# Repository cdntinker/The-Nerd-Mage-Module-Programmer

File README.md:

# This is __The Nerd Mage Module Programmer__  Project

The original intent of this project was to simplify pre-programming ESP modules.

I started out doing up a design to help a friend program ESP-M3 modules with OTA capable firmware that he could then solder into projects to be scattered around And never directly connected again.

And, of course, The rabbits showed up & started digging holes in my desktop...  As usual...

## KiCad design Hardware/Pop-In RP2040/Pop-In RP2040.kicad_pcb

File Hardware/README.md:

# This is __The Nerd Mage Module Programmer__  Project

Each of the subfolders here is basically a KiCAD project.  Yes, I know there's a lot of duplication here.  One of these days, I'll figure out how to make KiCAD re-use existing schematics & board files as "libraries".

- (KiCAD Customs)
  - Custom symbols, footprints, 3D models needed for this project
    - (Just the 3D models so far...)

## The various "editions"...

- (blank)
  - The base design with no module set up
- (standalone)
  - A version with a pin header instead of a module
- ESP-01F
  - Footprint added for an ESP-01F
- ESP-01S
  - Footprint added for an ESP-01S
- ESP-M3
  - Footprint added for an ESP-M3
- ESP-12
  - Footprint added for an ESP-12 (or ESP-07)
- ESP-Wroom-32
  - Footprint added for an ESP-Wroom-32
- Seeed Wio-RP2040
  - This one is VERY MUCH a WIP
  - Building & adding a footprint for the Seeed Studios Wio-RP2040 module
- BOM.ods
  - Sort of a manually created Bill of Materials

  ## To be done

  Need to work out how to add my custom symbols, footprints & 3D models in here...

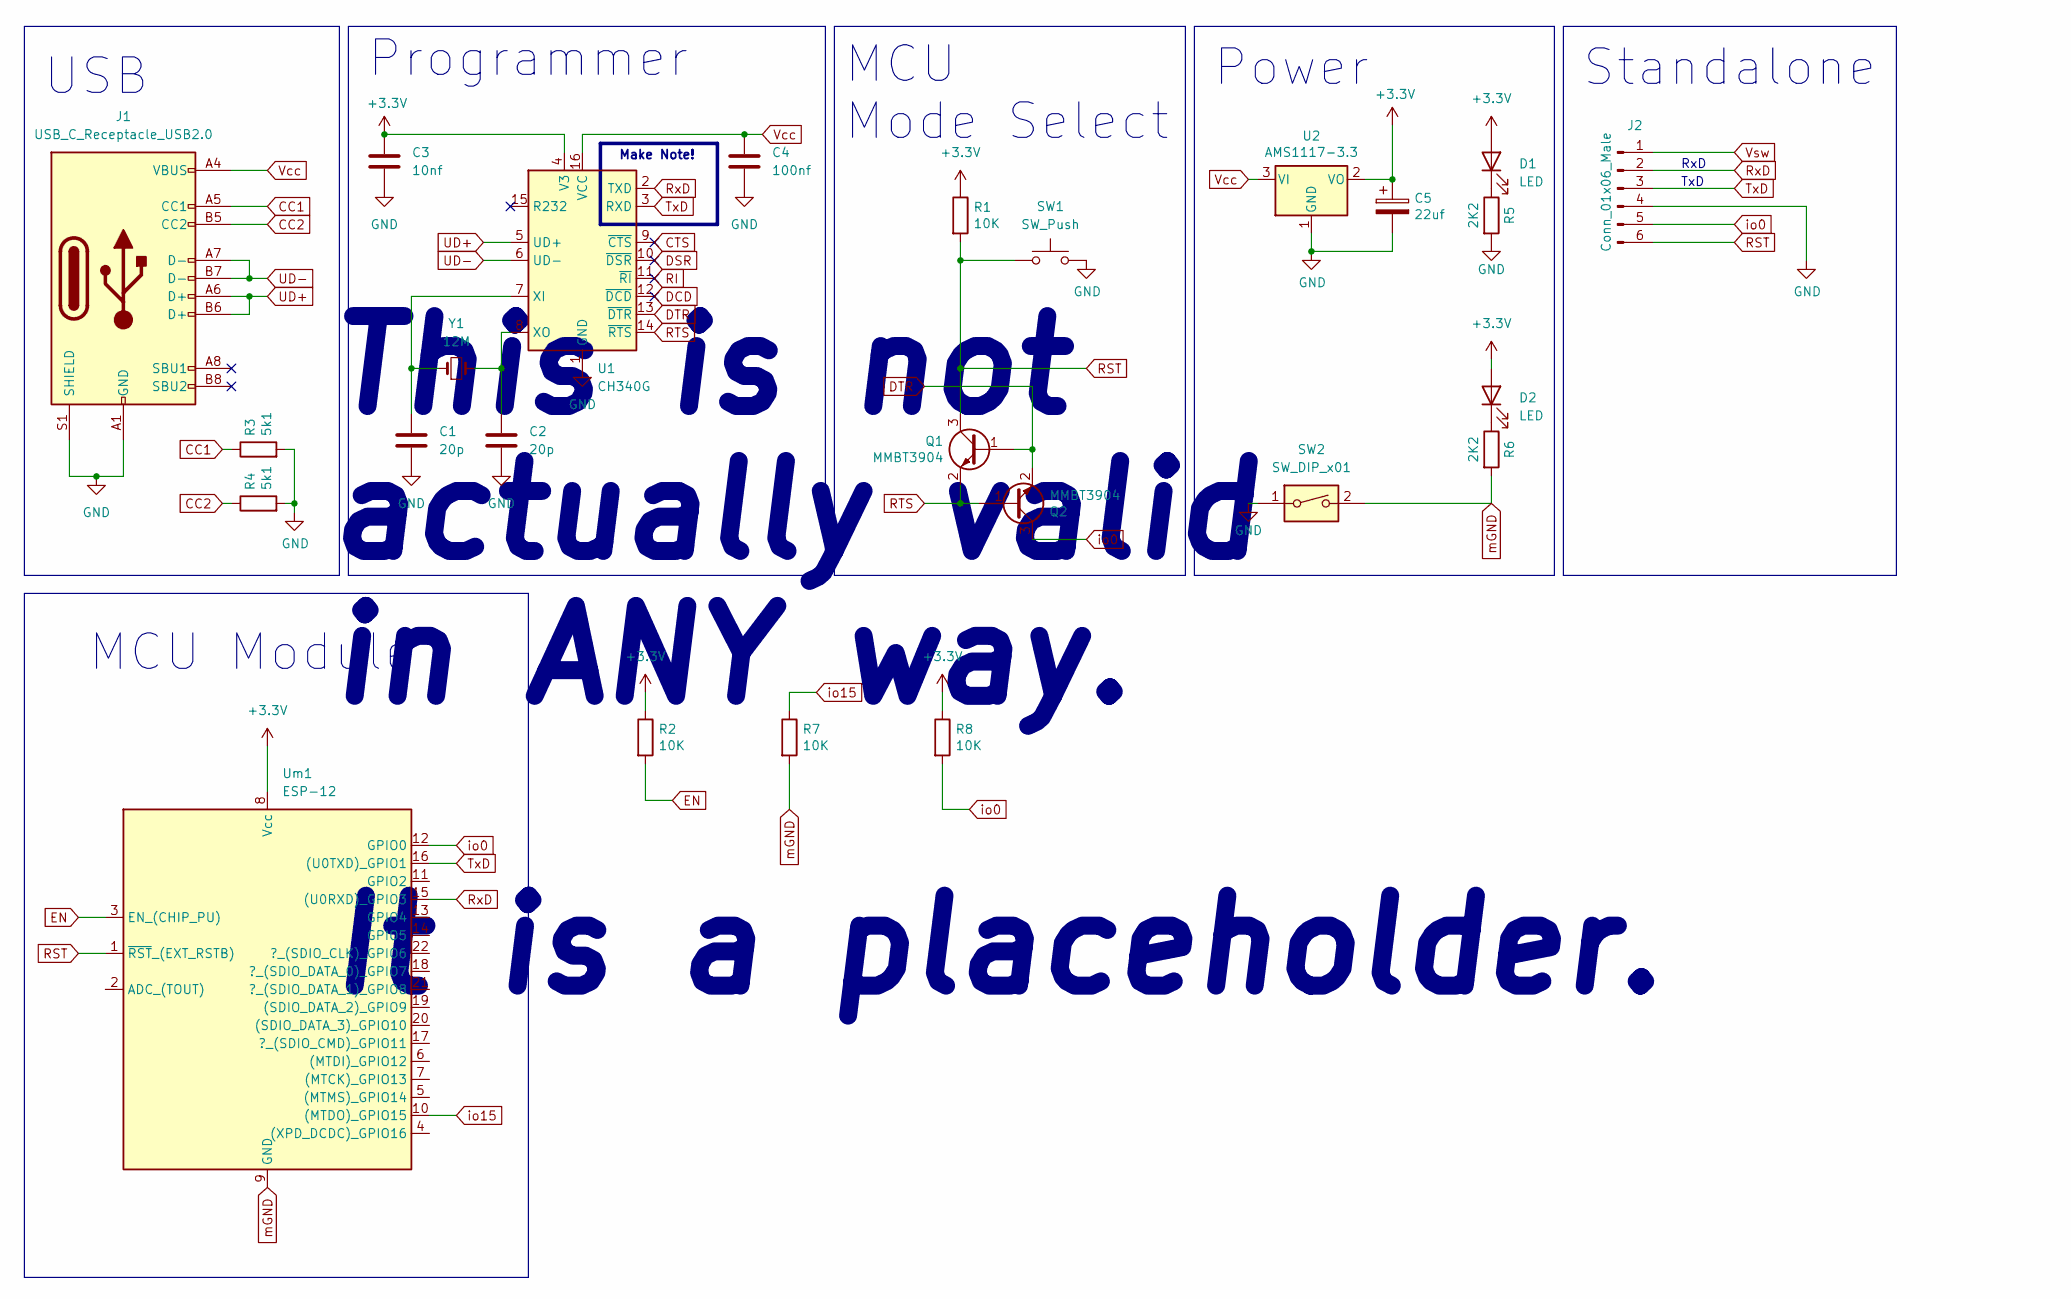
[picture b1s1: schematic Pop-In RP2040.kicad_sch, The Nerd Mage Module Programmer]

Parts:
C1, C2: 20p; C_0603_1608Metric_Pad1.08x0.95mm_HandSolder; LCSC C408549 (20pf C325469)
C3: 10nf; C_0603_1608Metric_Pad1.08x0.95mm_HandSolder; LCSC C161232
C4: 100nf; C_0603_1608Metric_Pad1.08x0.95mm_HandSolder; LCSC C235731
C5: 22uf; CP_EIA-6032-28_Kemet-C_Pad2.25x2.35mm_HandSolder
D1, D2: LED; LED_0805_2012Metric_Pad1.15x1.40mm_HandSolder
J1: USB_C_Receptacle_USB2.0; USB_C_Receptacle_HRO_TYPE-C-31-M-12
J2: Conn_01x06_Male; PinHeader_1x06_P2.54mm_Vertical
Q1, Q2: MMBT3904; SOT-23_Handsoldering
R1, R2, R7, R8: 10K; R_0603_1608Metric_Pad0.98x0.95mm_HandSolder
R3, R4: 5k1; R_0603_1608Metric_Pad0.98x0.95mm_HandSolder
R5, R6: 2K2; R_0603_1608Metric_Pad0.98x0.95mm_HandSolder
SW1: SW_Push; SW_Push_TS273014TP; LCSC C2858276
SW2: SW_DIP_x01; SW_DIP_SPSTx01_Slide_6.7x4.1mm_W7.62mm_P2.54mm_LowProfile
U1: CH340G; SOIC-16_3.9x9.9mm_P1.27mm; LCSC C14267
U2: AMS1117-3.3; SOT-223-3_TabPin2
Um1: ESP-12; ESP-12 (FlexyPin)
Y1: 12M; Crystal_SMD_5032-2Pin_5.0x3.2mm; LCSC C2842275

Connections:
+3.3V: C3.1, C5.1, D1.2 (A), D2.2 (A), R1.1, R2.1, R8.1, U1.4 (V3), U2.2 (VO), Um1.8 (Vcc)
CC1: J1.A5 (CC1), R3.1
CC2: J1.B5 (CC2), R4.1
CTS: U1.9 (~CTS)
DCD: U1.12 (~DCD)
DSR: U1.10 (~DSR)
DTR: Q1.1 (B), Q2.2 (E), U1.13 (~DTR)
EN: R2.2, Um1.3 (EN_(CHIP_PU))
GND: C1.2, C2.2, C3.2, C4.2, C5.2, J1.A1 (GND), J1.A12 (GND), J1.B1 (GND), J1.B12 (GND), J1.S1 (SHIELD), J2.4, R3.2, R4.2, R5.2, SW1.2, SW2.1, U1.1 (GND), U2.1 (GND)
unnamed: C1.1, U1.7 (XI), Y1.1
unnamed: C2.1, U1.8 (XO), Y1.2
unnamed: D1.1 (K), R5.1
unnamed: D2.1 (K), R6.1
RI: U1.11 (~RI)
RST: J2.6, Q1.3 (C), R1.2, SW1.1, Um1.1 (~RST_(EXT_RSTB))
RTS: Q1.2 (E), Q2.1 (B), U1.14 (~RTS)
RxD: J2.2, U1.2 (TXD), Um1.15 ((U0RXD)_GPIO3)
TxD: J2.3, U1.3 (RXD), Um1.16 ((U0TXD)_GPIO1)
UD+: J1.A6 (D+), J1.B6 (D+), U1.5 (UD+)
UD-: J1.A7 (D-), J1.B7 (D-), U1.6 (UD-)
Vcc: C4.1, J1.A4 (VBUS), J1.A9 (VBUS), J1.B4 (VBUS), J1.B9 (VBUS), U1.16 (VCC), U2.3 (VI)
io0: J2.5, Q2.3 (C), R8.2, Um1.12 (GPIO0)
io15: R7.1, Um1.10 ((MTDO)_GPIO15)
mGND: R6.2, R7.2, SW2.2, Um1.9 (GND)

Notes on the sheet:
Make Note!
Power
USB
MCU Mode Select
TxD
Standalone
This is not actually valid in ANY way. It is a placeholder.
RxD
MCU Module
Programmer

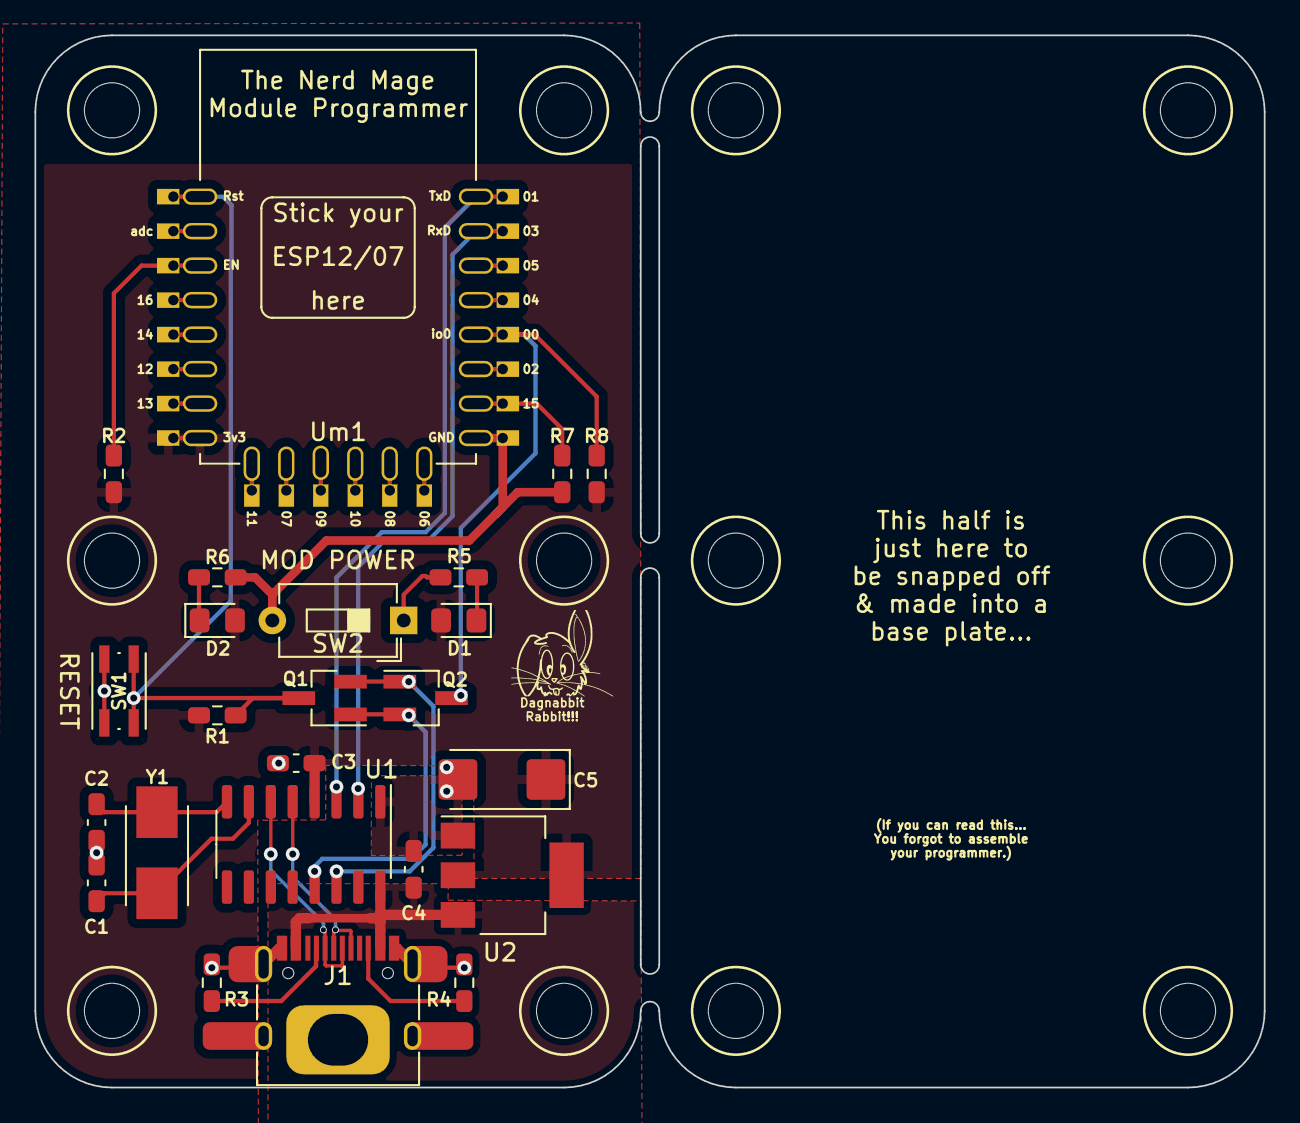
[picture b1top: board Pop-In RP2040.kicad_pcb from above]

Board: 2 copper layers, 71.3 x 61.0 mm, 24 parts (0 on the bottom side), 20 nets.

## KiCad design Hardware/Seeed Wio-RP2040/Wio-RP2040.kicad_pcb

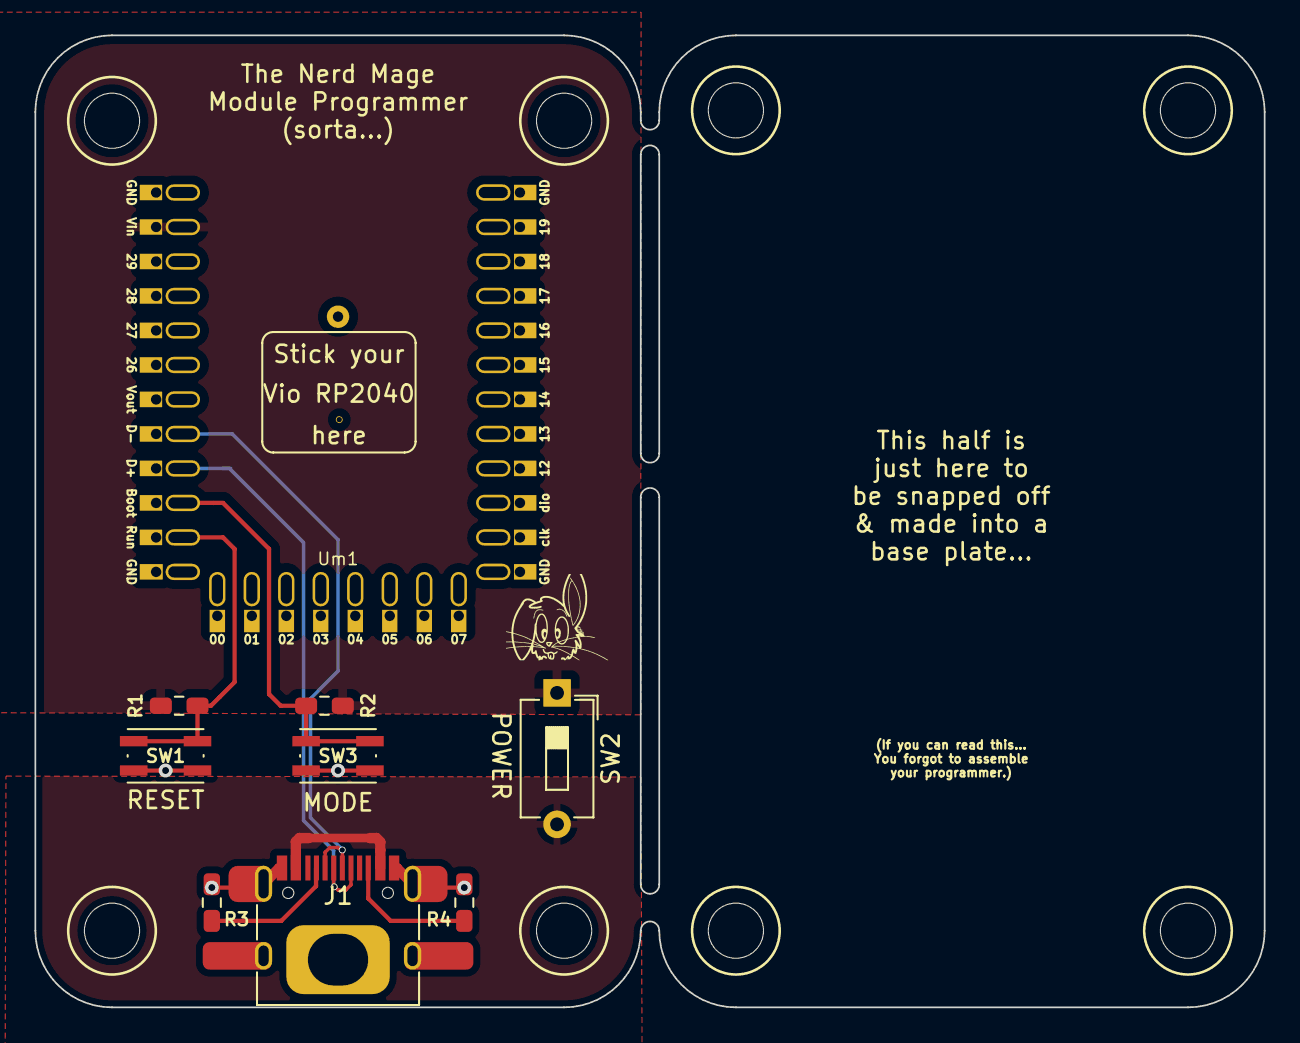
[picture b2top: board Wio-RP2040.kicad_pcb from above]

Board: 2 copper layers, 71.3 x 56.4 mm, 9 parts (0 on the bottom side), 9 nets.

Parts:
J1: USB_C_Receptacle_USB2.0; USB_C_Receptacle_HRO_TYPE-C-31-M-12
R1, R2: 10K; R_0603_1608Metric_Pad0.98x0.95mm_HandSolder
R3, R4: 5k1; R_0603_1608Metric_Pad0.98x0.95mm_HandSolder
SW1, SW3: SW_Push; SW_Push_TS273014TP
SW2: SW_DIP_x01; SW_DIP_SPSTx01_Slide_6.7x4.1mm_W7.62mm_P2.54mm_LowProfile
Um1: Wio-RP2040; Wio_RP2040 (FlexyPin)

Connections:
CC1: J1.A5 (CC1), R3.1
CC2: J1.B5 (CC2), R4.1
GND: J1.A1 (GND), J1.A12 (GND), J1.B1 (GND), J1.B12 (GND), J1.S1 (SHIELD), R3.2, R4.2, SW1.2, SW3.2, Um1.1 (GND), Um1.12 (GND), Um1.21 (GND), Um1.32 (GND), Um1.33 (GND)
RST: R1.2, SW1.1, Um1.11 (~Run_(RST))
UD+: J1.A6 (D+), J1.B6 (D+), Um1.9 (USB_D+)
UD-: J1.A7 (D-), J1.B7 (D-), Um1.8 (USB_D-)
Vcc: J1.A4 (VBUS), J1.A9 (VBUS), J1.B4 (VBUS), J1.B9 (VBUS), SW2.2
Vsw: R1.1, R2.1, SW2.1, Um1.2 (Vin)
mode: R2.2, SW3.1, Um1.10 (~Boot)

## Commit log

2023-06-29 Added M3 version
2023-06-29 01S & 01F added
2023-06-29 Fixin' up Edition names
2023-06-30 Startin' to add (KiCAD Customs) folder
2023-06-30 Fixed more 3D...
2023-06-30 Attempting to add my custom bits...
2023-06-30 updating the hardware README.md
2023-07-01 working on documentation
2023-07-01 oops
2023-07-01 Starting extensive schematic tidy-up
2023-07-02 WIP... Seeed Wio-RP2040
2023-07-03 werkin on da RP2040
2023-07-14 Getting up to rev 1
2023-07-14 gerbers ready(?)
2023-07-14 updating sheet info
2023-07-14 v1.0.0 gerbers submitted
2023-07-14 updated BOM & noted ESP-12 1.0.0 production
